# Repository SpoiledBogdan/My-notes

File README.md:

# My notes
This repository is primarily created for myself, to store various important things that I can remember by going here

FILES:

- functionPointer: example how to use function pointers
- Git: examples how to use Git (suddenly)

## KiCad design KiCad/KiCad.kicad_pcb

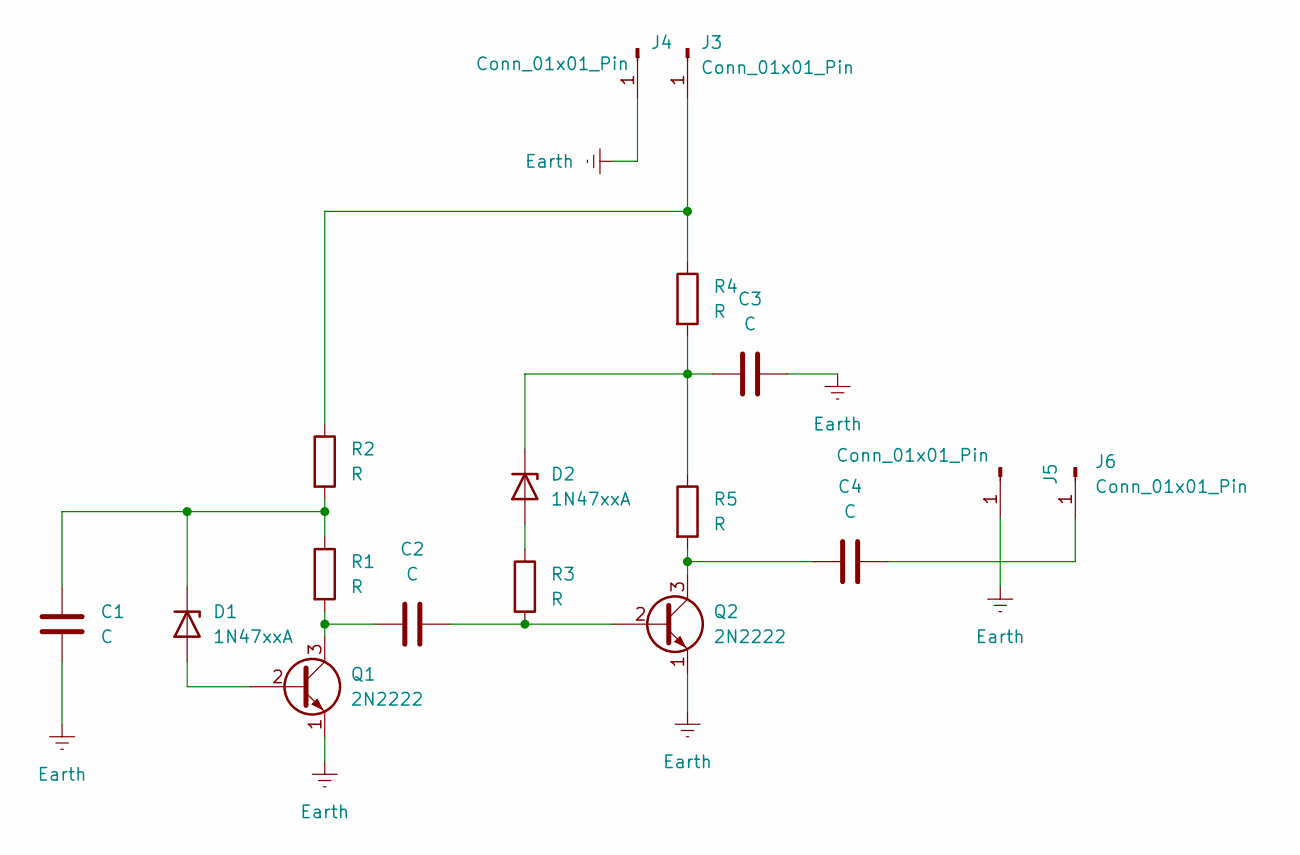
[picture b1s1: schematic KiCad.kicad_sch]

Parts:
C1, C2, C3, C4: C; C_0805_2012Metric
D1, D2: 1N47xxA; D_DO-41_SOD81_P10.16mm_Horizontal
J3, J4, J5, J6: Conn_01x01_Pin; SolderWire-0.1sqmm_1x01_D0.4mm_OD1mm
Q1, Q2: 2N2222; SOT-23
R1, R2, R3, R5: R; R_0805_2012Metric
R4: R; R_1206_3216Metric_Pad1.30x1.75mm_HandSolder

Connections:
Earth: C1.2, C3.2, J4.1, J5.1, Q1.1 (E), Q2.1 (E)
unnamed: D1.2 (A), Q1.2 (B)
unnamed: C1.1, D1.1 (K), R1.1, R2.2
unnamed: D2.2 (A), R3.1
unnamed: C3.1, D2.1 (K), R4.2, R5.1
unnamed: J3.1, R2.1, R4.1
unnamed: C4.2, J6.1
unnamed: C2.1, Q1.3 (C), R1.2
unnamed: C2.2, Q2.2 (B), R3.2
unnamed: C4.1, Q2.3 (C), R5.2

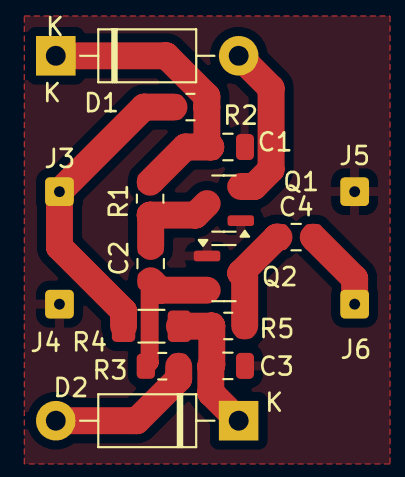
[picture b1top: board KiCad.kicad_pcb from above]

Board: 2 copper layers, 17 parts (0 on the bottom side), 10 nets.

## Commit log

2024-04-21 added new file
2024-07-09 adding few books
